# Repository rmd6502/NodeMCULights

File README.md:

# NodeMCULights
Lamp controller using MQTT and NodeMCU

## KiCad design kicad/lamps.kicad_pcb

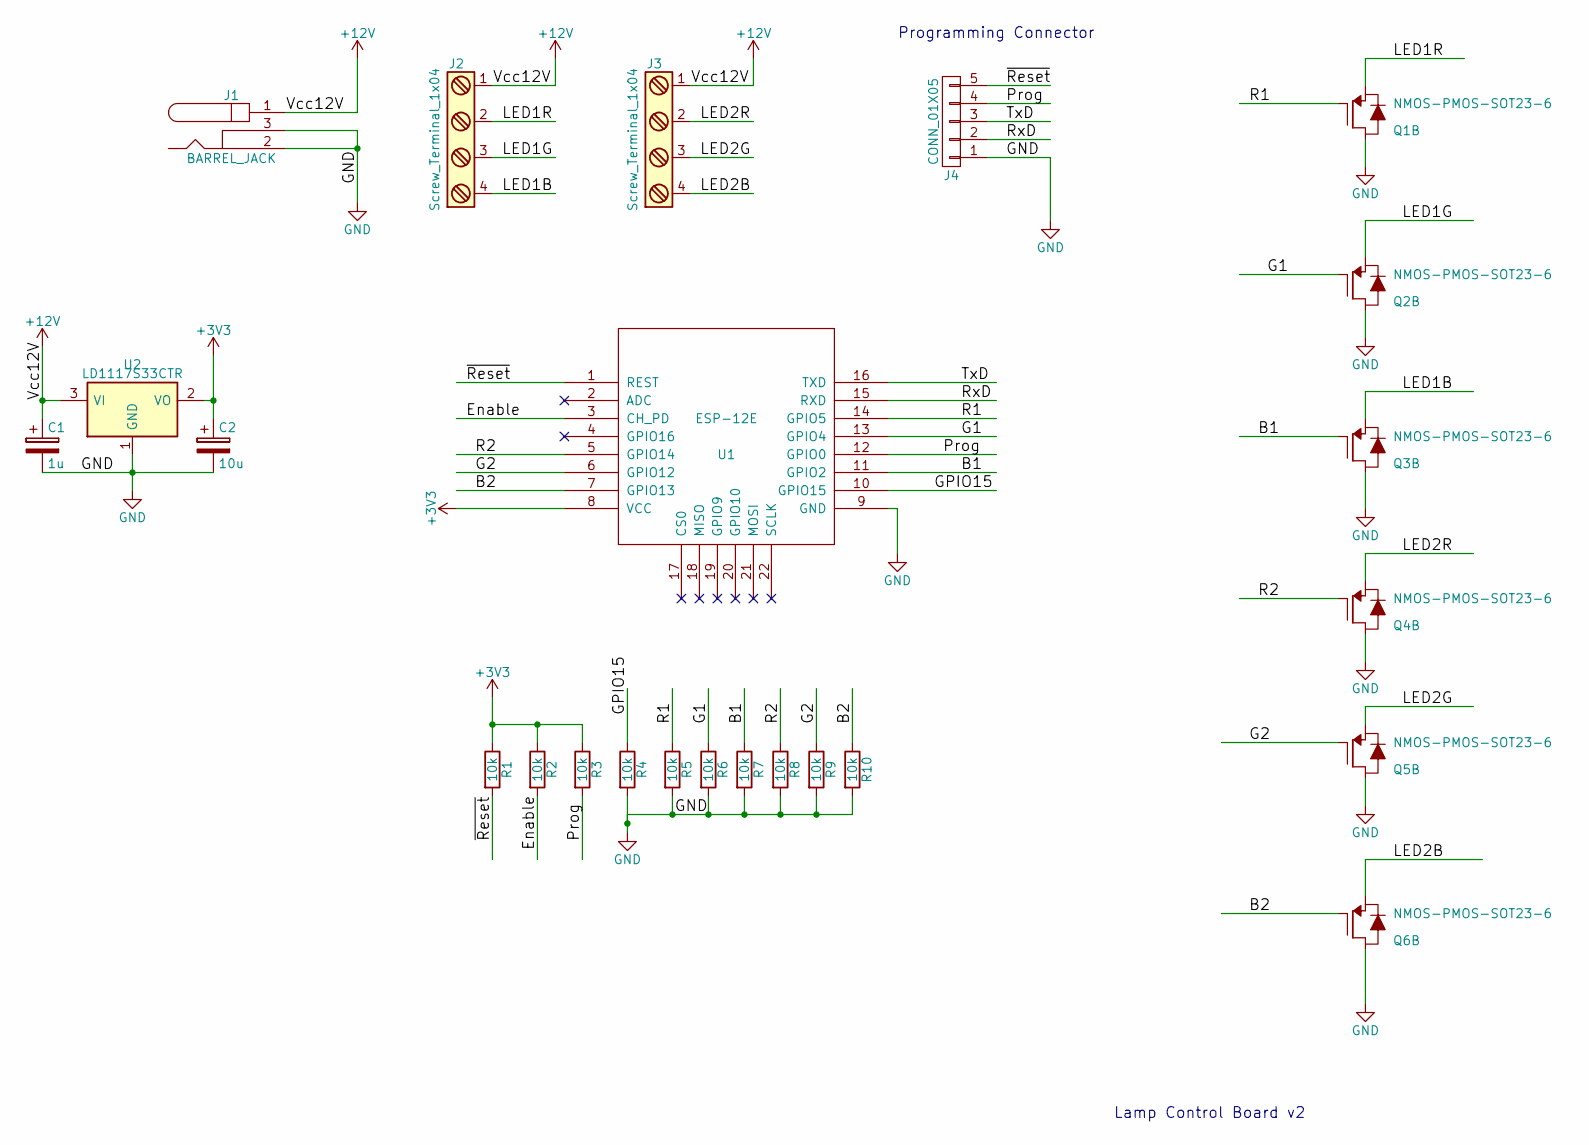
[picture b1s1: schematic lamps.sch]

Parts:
C1: 1u; CP_Elec_4x5.3
C2: 10u; CP_Elec_4x5.3
J1: BARREL_JACK
J2, J3: Screw_Terminal_1x04; TerminalBlock_Pheonix_MPT-2.54mm_4pol
J4: CONN_01X05; Pin_Header_Straight_1x05_Pitch2.54mm
Q1, Q2, Q3, Q4, Q5, Q6: NMOS-PMOS-SOT23-6; SOT-23-6
R1, R2, R3, R4, R5, R6, R7, R8, R9, R10: 10k; R_0603_HandSoldering
U1: ESP-12E
U2: LD1117S33CTR; SOT-223

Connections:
+3V3: C2.1, R1.1, R2.1, R3.1, U1.8 (VCC), U2.2 (VO)
+12V: C1.1, J1.1, J2.1, J3.1, U2.3 (VI)
/B1: Q3.3, R7.1, U1.11 (GPIO2)
/B2: Q6.3, R10.1, U1.7 (GPIO13)
/Enable: R2.2, U1.3 (CH_PD)
/G1: Q2.3, R6.1, U1.13 (GPIO4)
/G2: Q5.3, R9.1, U1.6 (GPIO12)
/GPIO15: R4.1, U1.10 (GPIO15)
/LED1B: J2.4, Q3.2
/LED1G: J2.3, Q2.2
/LED1R: J2.2, Q1.2
/LED2B: J3.4, Q6.2
/LED2G: J3.3, Q5.2
/LED2R: J3.2, Q4.2
/Prog: J4.4, R3.2, U1.12 (GPIO0)
/R1: Q1.3, R5.1, U1.14 (GPIO5)
/R2: Q4.3, R8.1, U1.5 (GPIO14)
/RxD: J4.2, U1.15 (RXD)
/TxD: J4.3, U1.16 (TXD)
/~Reset: J4.5, R1.2, U1.1 (REST)
GND: C1.2, C2.2, J1.2, J1.3, J4.1, Q1.4, Q2.4, Q3.4, Q4.4, Q5.4, Q6.4, R4.2, R5.2, R6.2, R7.2, R8.2, R9.2, R10.2, U1.9 (GND), U2.1 (GND)

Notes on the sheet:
Programming Connector
Lamp Control Board v2

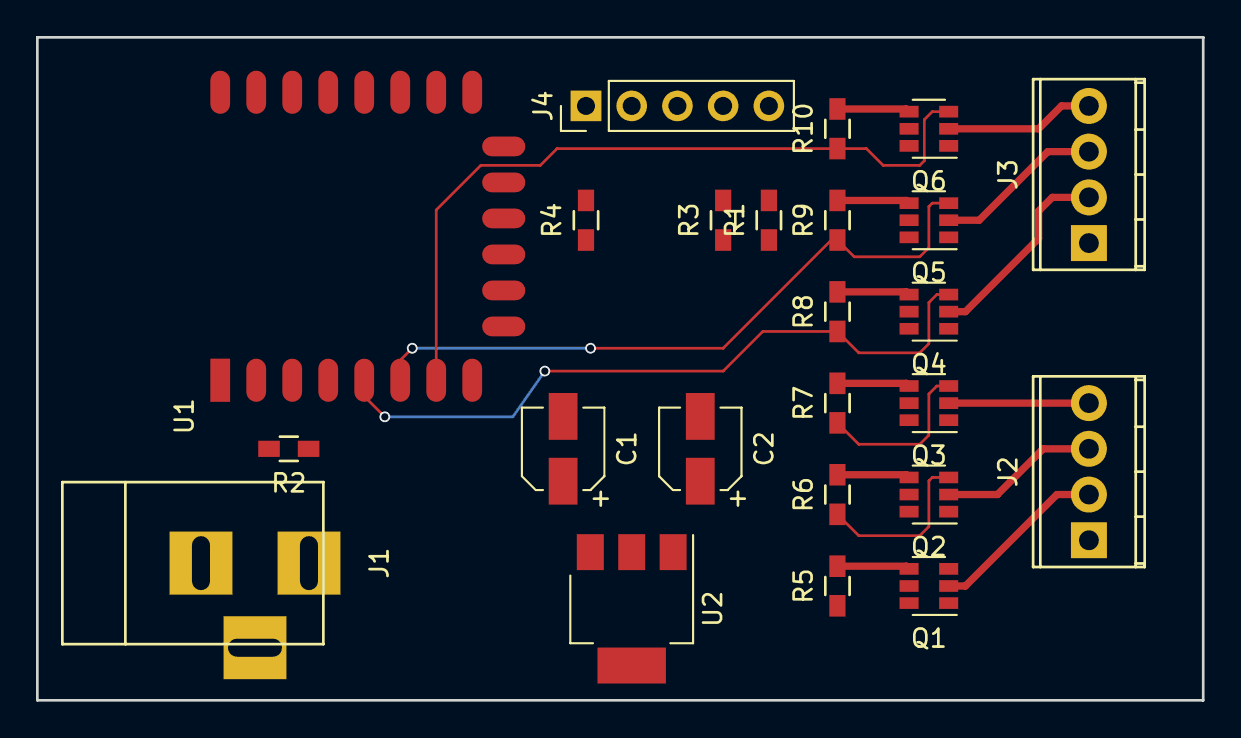
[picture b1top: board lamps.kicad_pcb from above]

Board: 2 copper layers, 64.8 x 36.8 mm, 24 parts (0 on the bottom side), 21 nets.

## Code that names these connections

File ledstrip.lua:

dofile("wificonfig.lua")
red1led=1   -- GPIO5
blue1led=6  -- GPIO12
green1led=7 -- GPIO13
red2led=2   -- GPIO4
blue2led=5  -- GPIO14
green2led=8 -- GPIO15

factor = 1023 / 255

m=mqtt.Client(config.clientName, 120)

function handleLed(m, message)
    print("received "..message)
    m:publish("/log", "received message "..message, 0, 0)
    val=tonumber(string.sub(message, 2), 16)
    print("message decoded to "..val)
    if val == nil then return end
    b = math.floor((val % 256) * factor)
    val = math.floor(val / 256)
    g = math.floor((val % 256) * factor)
    val = math.floor(val / 256)
    r = math.floor(val * factor)

    print(config.clientName.." set color to r"..r.."g"..g.."b"..b)
    m:publish("/log", config.clientName.." set color to r"..r.."g"..g.."b"..b, 0, 0)
    pwm.setduty(red1led, r)
    pwm.setduty(green1led, g)
    pwm.setduty(blue1led, b)
    pwm.setduty(red2led, r)
    pwm.setduty(green2led, g)
    pwm.setduty(blue2led, b)
end

function dispatch(client, topic, message)
  if message ~= nil and topic == config.subscribe then
    print("Dispatching "..topic.." "..message)
    handleLed(client, message)
  end
end

m:on("connect", function(m)
  m:publish("/log","Connected", 0, 0)
  print("Connected")

  m:subscribe(config.subscribe, 0, function(m) m:publish("/log",
    config.clientName.." subscribed to LED updates "..config.subscribe,
    0, 0) end)
  print("subscribed to LED updates")
end)

m:on("message", dispatch)

pwm.setup(red1led, 1000, 0)
pwm.start(red1led)
pwm.setup(green1led, 1000, 0)
pwm.start(green1led)
pwm.setup(blue1led, 1000, 0)
pwm.start(blue1led)
pwm.setup(red2led, 1000, 0)
pwm.start(red2led)
pwm.setup(green2led, 1000, 0)
pwm.start(green2led)
pwm.setup(blue2led, 1000, 0)
pwm.start(blue2led)

m:connect(config.mqttBroker,1883,0,1)
print("Connecting")

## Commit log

2017-04-09 various configurations for esp8266
2017-04-09 add rgb configs
2017-04-09 tweaks and logging
2017-04-18 lots of experimentation
2017-04-18 add minimal rotary encoder project
2017-04-20 prepare for github
2017-04-20 add example wificonfig
2017-04-20 bring in hardware files
2017-04-20 add HRP file
2017-04-20 add pdf schematic
2017-04-20 remote cruft
2017-04-20 fix bad error message
2017-04-20 remove bulk file
2017-04-20 start the pcb - the current layout pdf is definitely not the way Im going
2017-04-20 update sample wificonfig
2017-04-21 manual routing
2017-04-22 minor improvements
2017-04-23 incremental led update
